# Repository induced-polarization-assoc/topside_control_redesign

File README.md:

View this project on [CADLAB.io](https://cadlab.io/project/22681). 

# topside_control_redesign
Contains CAD, board, and schematics as well as development notes and firmware associated with the different modules of the system.

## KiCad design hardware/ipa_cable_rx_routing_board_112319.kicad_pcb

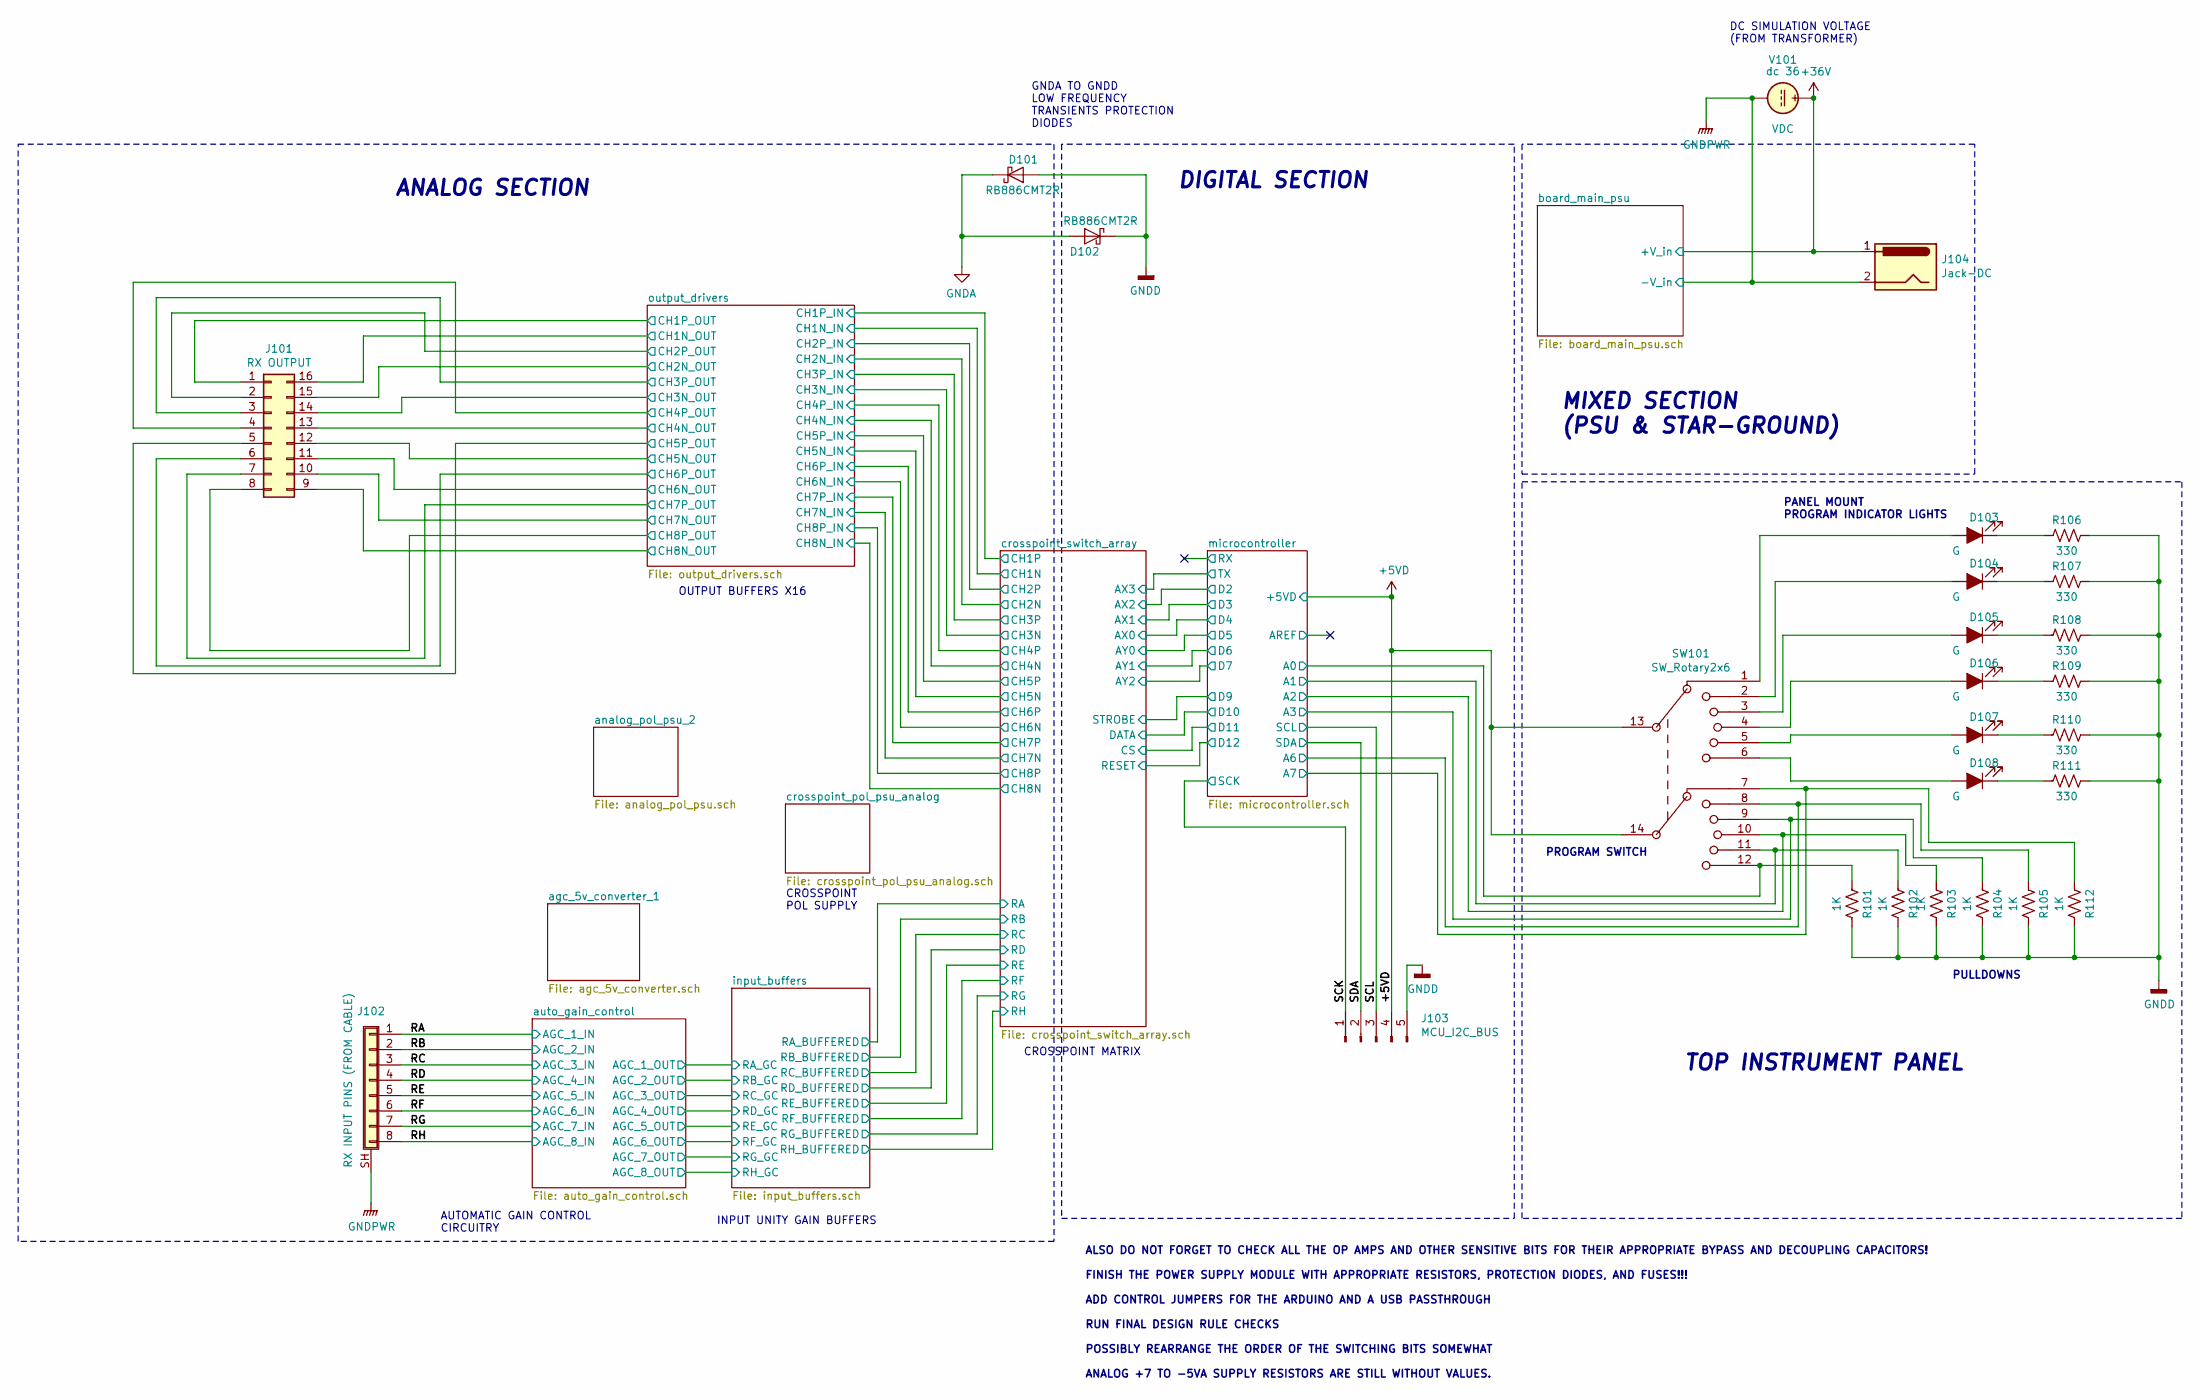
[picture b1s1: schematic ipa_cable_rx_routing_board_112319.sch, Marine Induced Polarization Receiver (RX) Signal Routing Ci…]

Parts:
D101, D102: RB886CMT2R; SOT-323_SC-70
D103, D104, D105, D106, D107, D108: G; PinHeader_1x02_P1.27mm_Vertical_SMD_Pin1Left
J101: RX OUTPUT; Samtec_HLE-108-02-xxx-DV-BE_2x08_P2.54mm_Horizontal
J102: RX INPUT PINS (FROM CABLE); Samtec_LSHM-105-xx.x-x-DV-S_2x05-1SH_P0.50mm_Vertical
J103: MCU_I2C_BUS; PinHeader_1x05_P1.27mm_Vertical_SMD_Pin1Right
J104: Jack-DC; TerminalBlock_TE_282834-3_1x03_P2.54mm_Horizontal
R101, R102, R103, R104, R105, R112: 1K; R_0805_2012Metric
R106, R107, R108, R109, R110, R111: 330; R_0805_2012Metric
SW101: SW_Rotary2x6; IDC-Header_2x07_P2.54mm_Vertical
V101: VDC; Symbol_GNU-Logo_SilkscreenTop

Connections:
+5VD: J103.4, SW101.13, SW101.14; also elsewhere on the board
+36V: J104.1, V101.1; also elsewhere on the board
/RA: J102.1; also elsewhere on the board
/RB: J102.2; also elsewhere on the board
/RC: J102.3; also elsewhere on the board
/RD: J102.4; also elsewhere on the board
/RE: J102.5; also elsewhere on the board
/RF: J102.6; also elsewhere on the board
/RG: J102.7; also elsewhere on the board
/RH: J102.8; also elsewhere on the board
/SCK: J103.1; also elsewhere on the board
/SCL: J103.3; also elsewhere on the board
/SDA: J103.2; also elsewhere on the board
/microcontroller/A0: R101.2, SW101.12; also elsewhere on the board
/microcontroller/A1: R102.2, SW101.11; also elsewhere on the board
/microcontroller/A2: R103.2, SW101.10; also elsewhere on the board
/microcontroller/A3: R104.2, SW101.9; also elsewhere on the board
/microcontroller/A6: R105.2, SW101.8; also elsewhere on the board
/microcontroller/A7: R112.2, SW101.7; also elsewhere on the board
/output_drivers/CH1N_OUT: J101.16; also elsewhere on the board
/output_drivers/CH1P_OUT: J101.1; also elsewhere on the board
/output_drivers/CH2N_OUT: J101.15; also elsewhere on the board
/output_drivers/CH2P_OUT: J101.2; also elsewhere on the board
/output_drivers/CH3N_OUT: J101.14; also elsewhere on the board
/output_drivers/CH3P_OUT: J101.3; also elsewhere on the board
/output_drivers/CH4N_OUT: J101.13; also elsewhere on the board
/output_drivers/CH4P_OUT: J101.4; also elsewhere on the board
/output_drivers/CH5N_OUT: J101.12; also elsewhere on the board
/output_drivers/CH5P_OUT: J101.5; also elsewhere on the board
/output_drivers/CH6N_OUT: J101.11; also elsewhere on the board
/output_drivers/CH6P_OUT: J101.6; also elsewhere on the board
/output_drivers/CH7N_OUT: J101.10; also elsewhere on the board
/output_drivers/CH7P_OUT: J101.7; also elsewhere on the board
/output_drivers/CH8N_OUT: J101.9; also elsewhere on the board
/output_drivers/CH8P_OUT: J101.8; also elsewhere on the board
GNDA: D101.1 (K), D102.2 (A); also elsewhere on the board
GNDD: D101.2 (A), D102.1 (K), J103.5, R101.1, R102.1, R103.1, R104.1, R105.1, R106.1, R107.1, R108.1, R109.1, R110.1, R111.1, R112.1; also elsewhere on the board
GNDPWR: J102.SH (Shield), J104.2, V101.2; also elsewhere on the board
unnamed: D103.1 (K), R106.2
unnamed: D103.2 (A), SW101.1
unnamed: D104.1 (K), R107.2
unnamed: D104.2 (A), SW101.2
unnamed: D105.1 (K), R108.2
unnamed: D105.2 (A), SW101.3
unnamed: D106.1 (K), R109.2
unnamed: D106.2 (A), SW101.4
unnamed: D107.1 (K), R110.2
unnamed: D107.2 (A), SW101.5
unnamed: D108.1 (K), R111.2
unnamed: D108.2 (A), SW101.6

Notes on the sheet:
INPUT UNITY GAIN BUFFERS
CROSSPOINT MATRIX
ALSO DO NOT FORGET TO CHECK ALL THE OP AMPS AND OTHER SENSITIVE BITS FOR THEIR APPROPRIATE BYPASS AND DECOUPLING CAPACITORS! FINISH THE POWER SUPPLY MODULE WITH APPROPRIATE RESISTORS, PROTECTION DIODES, AND FUSES!!! ADD CONTROL JUMPERS FOR THE ARDUINO AND A USB PASSTHROUGH RUN FINAL DESIGN RULE CHE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
OUTPUT BUFFERS X16
CROSSPOINT POL SUPPLY
DIGITAL SECTION
ANALOG SECTION
MIXED SECTION (PSU & STAR-GROUND)
PROGRAM SWITCH
PANEL MOUNT PROGRAM INDICATOR LIGHTS
TOP INSTRUMENT PANEL
PULLDOWNS
AUTOMATIC GAIN CONTROL CIRCUITRY
GNDA TO GNDD LOW FREQUENCY TRANSIENTS PROTECTION DIODES
DC SIMULATION VOLTAGE (FROM TRANSFORMER)

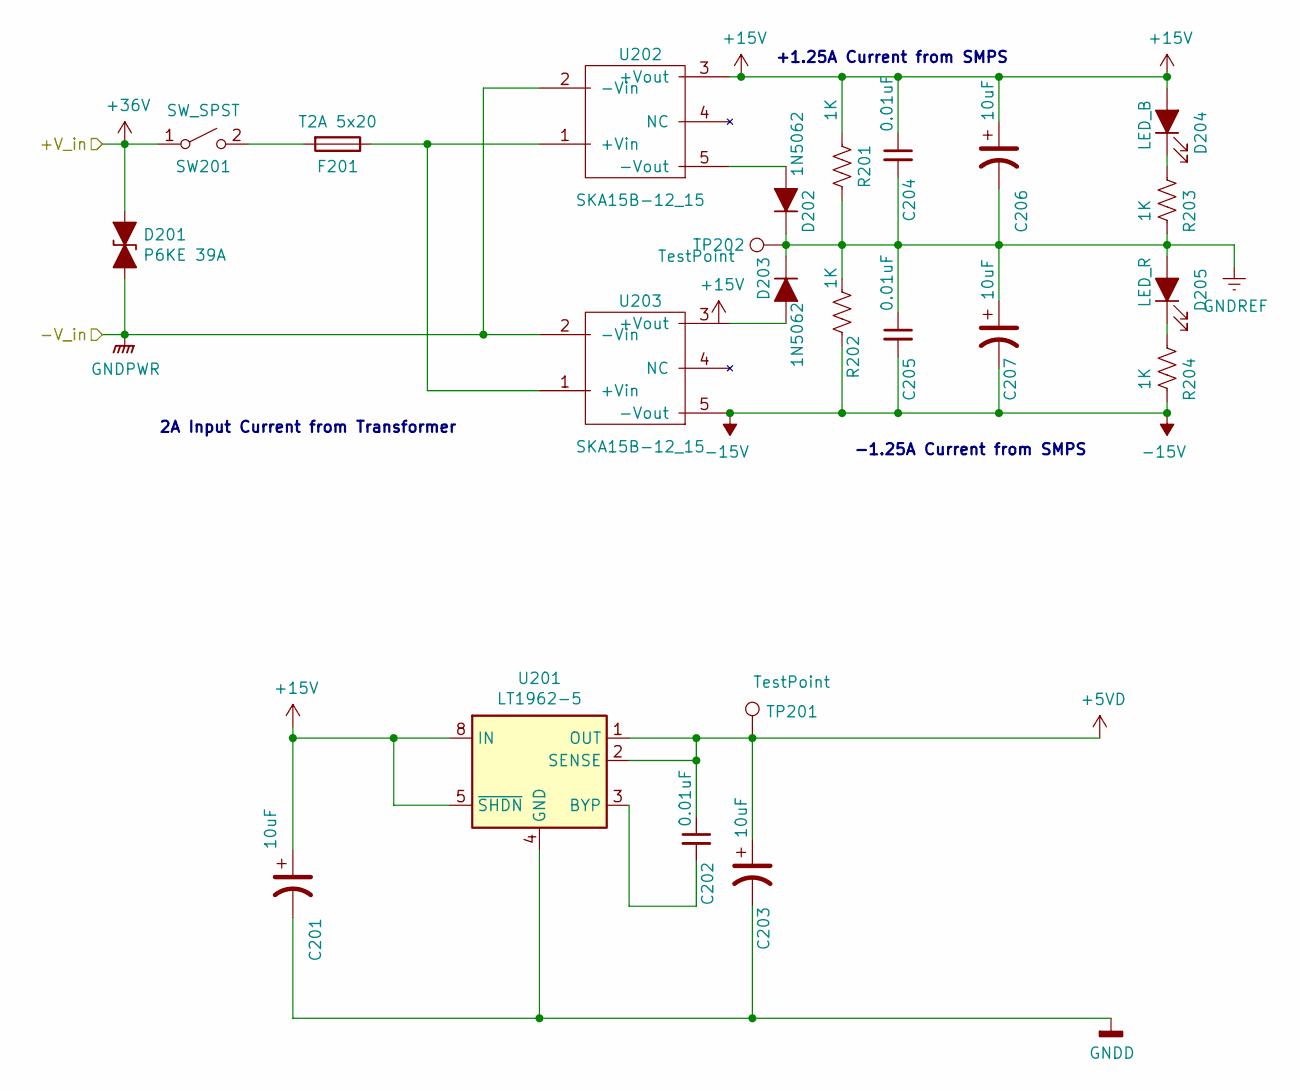
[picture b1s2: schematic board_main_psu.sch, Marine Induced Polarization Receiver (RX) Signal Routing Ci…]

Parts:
C201, C203, C206, C207: 10uF; CP_Elec_4x5.4
C202, C204, C205: 0.01uF; C_0805_2012Metric
D201: P6KE 39A; D_SMB
D202, D203: 1N5062; D_DO-15_P12.70mm_Horizontal
D204: LED_B; PinHeader_1x02_P1.27mm_Vertical_SMD_Pin1Left
D205: LED_R; PinHeader_1x02_P1.27mm_Vertical_SMD_Pin1Left
F201: T2A 5x20; Fuse_BelFuse_0ZRE0125FF_L21.2mm_W5.3mm
R201, R202, R203, R204: 1K; R_0805_2012Metric
SW201: SW_SPST; PinHeader_1x02_P1.27mm_Vertical_SMD_Pin1Left
TP201, TP202: TestPoint; TestPoint_Pad_D2.0mm
U201: LT1962-5; MSOP-8_3x3mm_P0.65mm
U202, U203: SKA15B-12_15; Converter_DCDC_MEANWELL_SKA15B_XXX_THT

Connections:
+5VD: C202.1, C203.1, TP201.1, U201.1 (OUT), U201.2 (SENSE); also elsewhere on the board
+15V: C201.1, C204.1, C206.1, D204.2 (A), R201.1, U201.5 (~SHDN), U201.8 (IN), U202.3 (+Vout); also elsewhere on the board
+36V: D201.1 (A1), SW201.1 (A); also elsewhere on the board
-15V: C205.2, C207.2, R202.2, R204.2, U203.5 (-Vout); also elsewhere on the board
GNDD: C201.2, C203.2, U201.4 (GND); also elsewhere on the board
GNDPWR: D201.2 (A2), U202.2 (-Vin), U203.2 (-Vin); also elsewhere on the board
GNDREF: C204.2, C205.1, C206.2, C207.1, D202.1 (K), D203.1 (K), D205.2 (A), R201.2, R202.1, R203.2, TP202.1
unnamed: C202.2, U201.3 (BYP)
unnamed: D202.2 (A), U202.5 (-Vout)
unnamed: D203.2 (A), U203.3 (+Vout)
unnamed: D204.1 (K), R203.1
unnamed: D205.1 (K), R204.1
unnamed: F201.1, U202.1 (+Vin), U203.1 (+Vin)
unnamed: F201.2, SW201.2 (B)

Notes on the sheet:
2A Input Current from Transformer
+1.25A Current from SMPS
-1.25A Current from SMPS

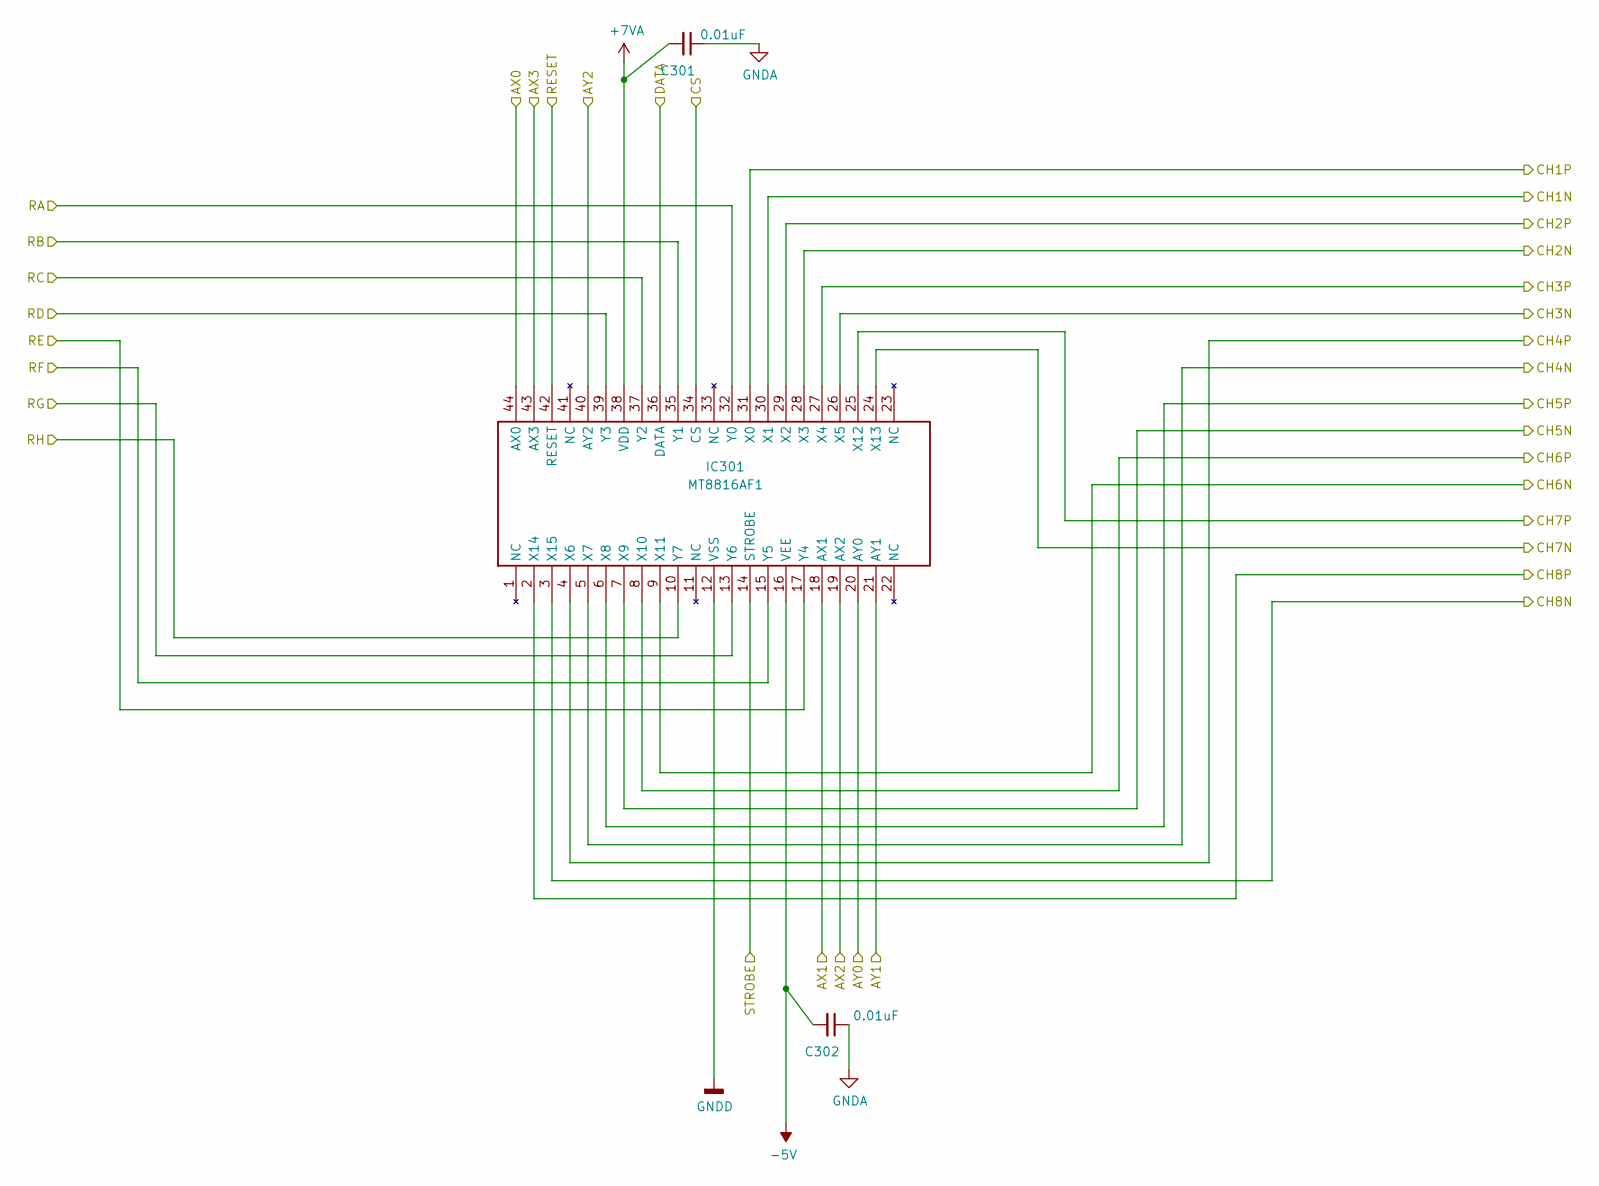
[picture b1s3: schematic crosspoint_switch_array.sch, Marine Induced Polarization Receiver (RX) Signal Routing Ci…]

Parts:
C301, C302: 0.01uF; C_0805_2012Metric
IC301: MT8816AF1; TQFP-44_10x10mm_P0.8mm

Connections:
+7VA: C301.2, IC301.38 (VDD); also elsewhere on the board
-5V: C302.2, IC301.16 (VEE); also elsewhere on the board
/crosspoint_switch_array/AX0: IC301.44 (AX0); also elsewhere on the board
/crosspoint_switch_array/AX1: IC301.18 (AX1); also elsewhere on the board
/crosspoint_switch_array/AX2: IC301.19 (AX2); also elsewhere on the board
/crosspoint_switch_array/AX3: IC301.43 (AX3); also elsewhere on the board
/crosspoint_switch_array/AY0: IC301.20 (AY0); also elsewhere on the board
/crosspoint_switch_array/AY1: IC301.21 (AY1); also elsewhere on the board
/crosspoint_switch_array/AY2: IC301.40 (AY2); also elsewhere on the board
/crosspoint_switch_array/CH1N: IC301.30 (X1); also elsewhere on the board
/crosspoint_switch_array/CH1P: IC301.31 (X0); also elsewhere on the board
/crosspoint_switch_array/CH2N: IC301.28 (X3); also elsewhere on the board
/crosspoint_switch_array/CH2P: IC301.29 (X2); also elsewhere on the board
/crosspoint_switch_array/CH3N: IC301.26 (X5); also elsewhere on the board
/crosspoint_switch_array/CH3P: IC301.27 (X4); also elsewhere on the board
/crosspoint_switch_array/CH4N: IC301.5 (X7); also elsewhere on the board
/crosspoint_switch_array/CH4P: IC301.4 (X6); also elsewhere on the board
/crosspoint_switch_array/CH5N: IC301.7 (X9); also elsewhere on the board
/crosspoint_switch_array/CH5P: IC301.6 (X8); also elsewhere on the board
/crosspoint_switch_array/CH6N: IC301.9 (X11); also elsewhere on the board
/crosspoint_switch_array/CH6P: IC301.8 (X10); also elsewhere on the board
/crosspoint_switch_array/CH7N: IC301.24 (X13); also elsewhere on the board
/crosspoint_switch_array/CH7P: IC301.25 (X12); also elsewhere on the board
/crosspoint_switch_array/CH8N: IC301.3 (X15); also elsewhere on the board
/crosspoint_switch_array/CH8P: IC301.2 (X14); also elsewhere on the board
/crosspoint_switch_array/CS: IC301.34 (CS); also elsewhere on the board
/crosspoint_switch_array/RA: IC301.32 (Y0); also elsewhere on the board
/crosspoint_switch_array/RB: IC301.35 (Y1); also elsewhere on the board
/crosspoint_switch_array/RC: IC301.37 (Y2); also elsewhere on the board
/crosspoint_switch_array/RD: IC301.39 (Y3); also elsewhere on the board
/crosspoint_switch_array/RE: IC301.17 (Y4); also elsewhere on the board
/crosspoint_switch_array/RF: IC301.15 (Y5); also elsewhere on the board
/crosspoint_switch_array/RG: IC301.13 (Y6); also elsewhere on the board
/crosspoint_switch_array/RH: IC301.10 (Y7); also elsewhere on the board
/microcontroller/D9: IC301.14 (STROBE); also elsewhere on the board
/microcontroller/D10: IC301.36 (DATA); also elsewhere on the board
/microcontroller/D12: IC301.42 (RESET); also elsewhere on the board
GNDA: C301.1, C302.1; also elsewhere on the board
GNDD: IC301.12 (VSS); also elsewhere on the board

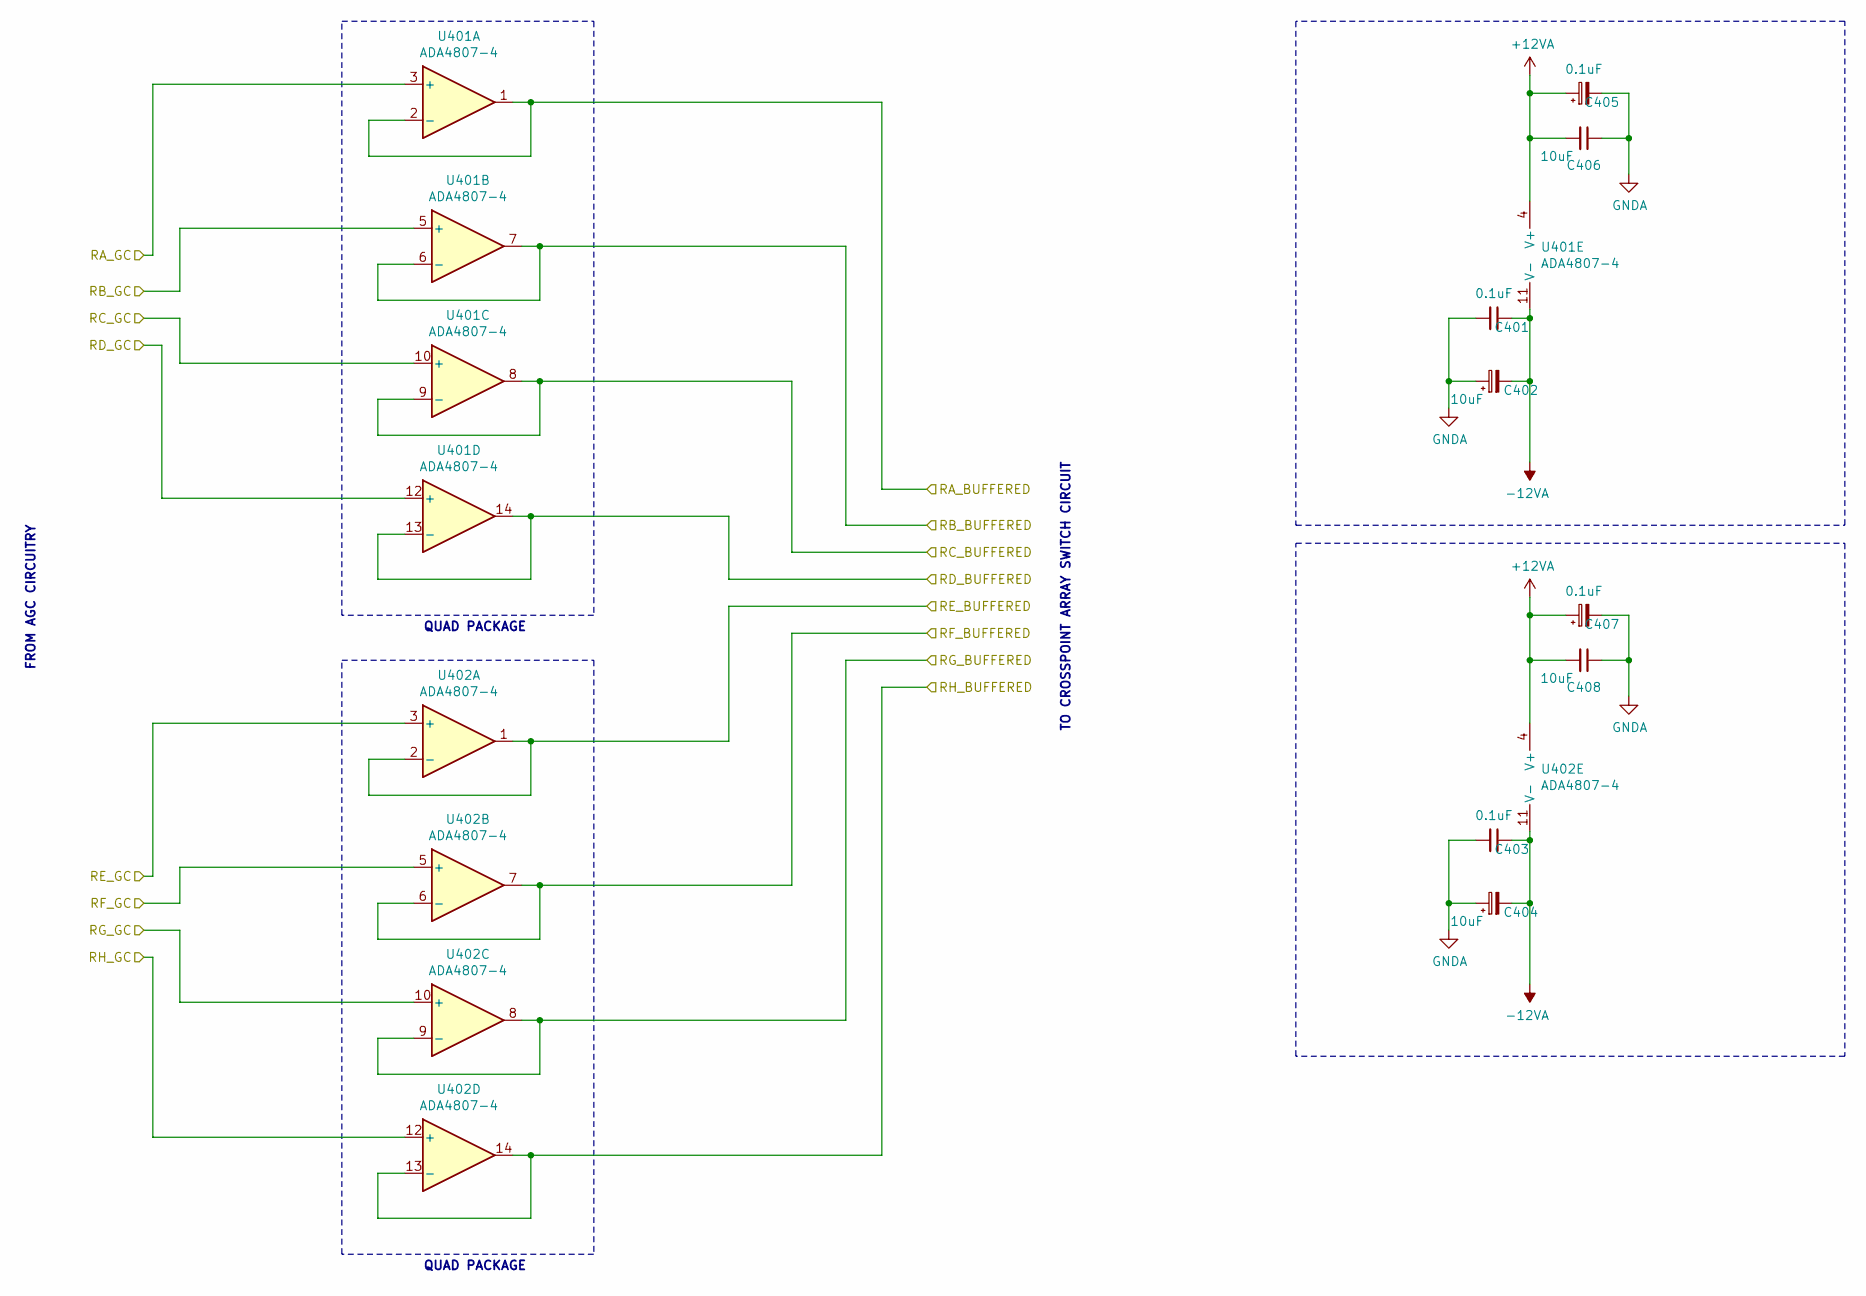
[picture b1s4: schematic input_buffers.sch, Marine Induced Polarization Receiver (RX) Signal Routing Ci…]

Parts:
C401, C403, C405, C407: 0.1uF; C_0805_2012Metric
C402, C404, C406, C408: 10uF; CP_Elec_4x5.4
U401, U402: ADA4807-4; TSSOP-14_4.4x5mm_P0.65mm

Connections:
+12VA: C405.1, C406.2, C407.1, C408.2, U401.4 (V+), U402.4 (V+); also elsewhere on the board
-12VA: C401.1, C402.2, C403.1, C404.2, U401.11 (V-), U402.11 (V-); also elsewhere on the board
/auto_gain_control/AGC_1_OUT: U401.3 (+); also elsewhere on the board
/auto_gain_control/AGC_2_OUT: U401.5 (+); also elsewhere on the board
/auto_gain_control/AGC_3_OUT: U401.10 (+); also elsewhere on the board
/auto_gain_control/AGC_4_OUT: U401.12 (+); also elsewhere on the board
/auto_gain_control/AGC_5_OUT: U402.3 (+); also elsewhere on the board
/auto_gain_control/AGC_6_OUT: U402.5 (+); also elsewhere on the board
/auto_gain_control/AGC_7_OUT: U402.10 (+); also elsewhere on the board
/auto_gain_control/AGC_8_OUT: U402.12 (+); also elsewhere on the board
/crosspoint_switch_array/RA: U401.1, U401.2 (-); also elsewhere on the board
/crosspoint_switch_array/RB: U401.6 (-), U401.7; also elsewhere on the board
/crosspoint_switch_array/RC: U401.8, U401.9 (-); also elsewhere on the board
/crosspoint_switch_array/RD: U401.13 (-), U401.14; also elsewhere on the board
/crosspoint_switch_array/RE: U402.1, U402.2 (-); also elsewhere on the board
/crosspoint_switch_array/RF: U402.6 (-), U402.7; also elsewhere on the board
/crosspoint_switch_array/RG: U402.8, U402.9 (-); also elsewhere on the board
/crosspoint_switch_array/RH: U402.13 (-), U402.14; also elsewhere on the board
GNDA: C401.2, C402.1, C403.2, C404.1, C405.2, C406.1, C407.2, C408.1; also elsewhere on the board

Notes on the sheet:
QUAD PACKAGE
FROM AGC CIRCUITRY
TO CROSSPOINT ARRAY SWITCH CIRCUIT

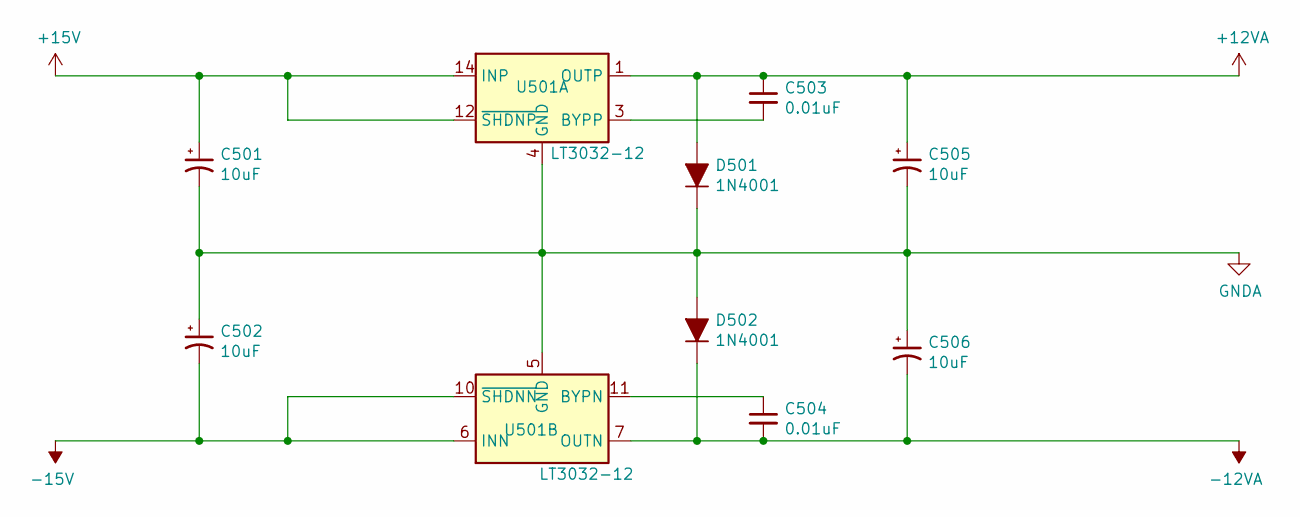
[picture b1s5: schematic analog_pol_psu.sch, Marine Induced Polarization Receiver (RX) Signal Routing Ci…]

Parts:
C501, C502, C505, C506: 10uF; CP_Elec_4x5.4
C503, C504: 0.01uF; C_0805_2012Metric
D501, D502: 1N4001; D_DO-41_SOD81_P10.16mm_Horizontal
U501: LT3032-12; Linear_DE14MA

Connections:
+12VA: C503.1, C505.1, D501.2 (A), U501.1 (OUTP); also elsewhere on the board
+15V: C501.1, U501.12 (~SHDNP), U501.14 (INP); also elsewhere on the board
-12VA: C504.2, C506.2, D502.1 (K), U501.7 (OUTN); also elsewhere on the board
-15V: C502.2, U501.6 (INN), U501.9 (INN), U501.10 (~SHDNN); also elsewhere on the board
GNDA: C501.2, C502.1, C505.2, C506.1, D501.1 (K), D502.2 (A), U501.4 (GND), U501.5 (GND); also elsewhere on the board
unnamed: C503.2, U501.3 (BYPP)
unnamed: C504.1, U501.11 (BYPN)

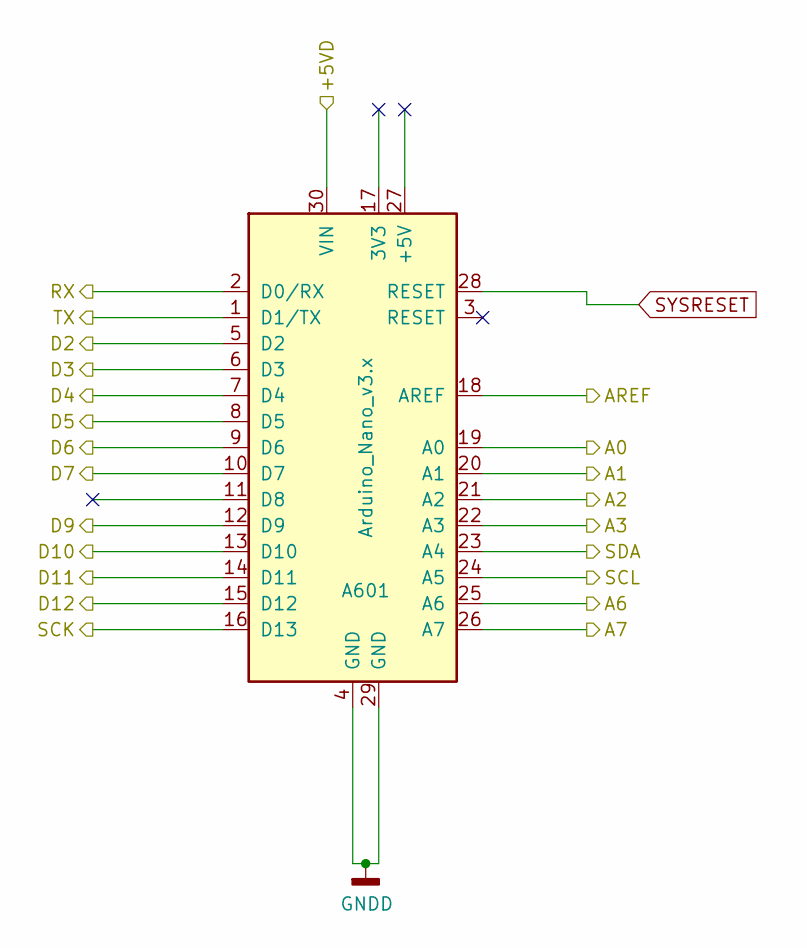
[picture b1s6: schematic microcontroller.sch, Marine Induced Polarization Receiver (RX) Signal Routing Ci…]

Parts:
A601: Arduino_Nano_v3.x; Arduino_Nano

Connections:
+5VD: A601.30 (VIN); also elsewhere on the board
/SCK: A601.16 (D13); also elsewhere on the board
/SCL: A601.24 (A5); also elsewhere on the board
/SDA: A601.23 (A4); also elsewhere on the board
/crosspoint_switch_array/AX0: A601.7 (D4); also elsewhere on the board
/crosspoint_switch_array/AX1: A601.6 (D3); also elsewhere on the board
/crosspoint_switch_array/AX2: A601.5 (D2); also elsewhere on the board
/crosspoint_switch_array/AX3: A601.1 (D1/TX); also elsewhere on the board
/crosspoint_switch_array/AY0: A601.8 (D5); also elsewhere on the board
/crosspoint_switch_array/AY1: A601.9 (D6); also elsewhere on the board
/crosspoint_switch_array/AY2: A601.10 (D7); also elsewhere on the board
/crosspoint_switch_array/CS: A601.14 (D11); also elsewhere on the board
/microcontroller/A0: A601.19 (A0); also elsewhere on the board
/microcontroller/A1: A601.20 (A1); also elsewhere on the board
/microcontroller/A2: A601.21 (A2); also elsewhere on the board
/microcontroller/A3: A601.22 (A3); also elsewhere on the board
/microcontroller/A6: A601.25 (A6); also elsewhere on the board
/microcontroller/A7: A601.26 (A7); also elsewhere on the board
/microcontroller/AREF: A601.18 (AREF)
/microcontroller/D9: A601.12 (D9); also elsewhere on the board
/microcontroller/D10: A601.13 (D10); also elsewhere on the board
/microcontroller/D12: A601.15 (D12); also elsewhere on the board
/microcontroller/RX: A601.2 (D0/RX)
GNDD: A601.4 (GND), A601.29 (GND); also elsewhere on the board
SYSRESET: A601.28 (RESET)

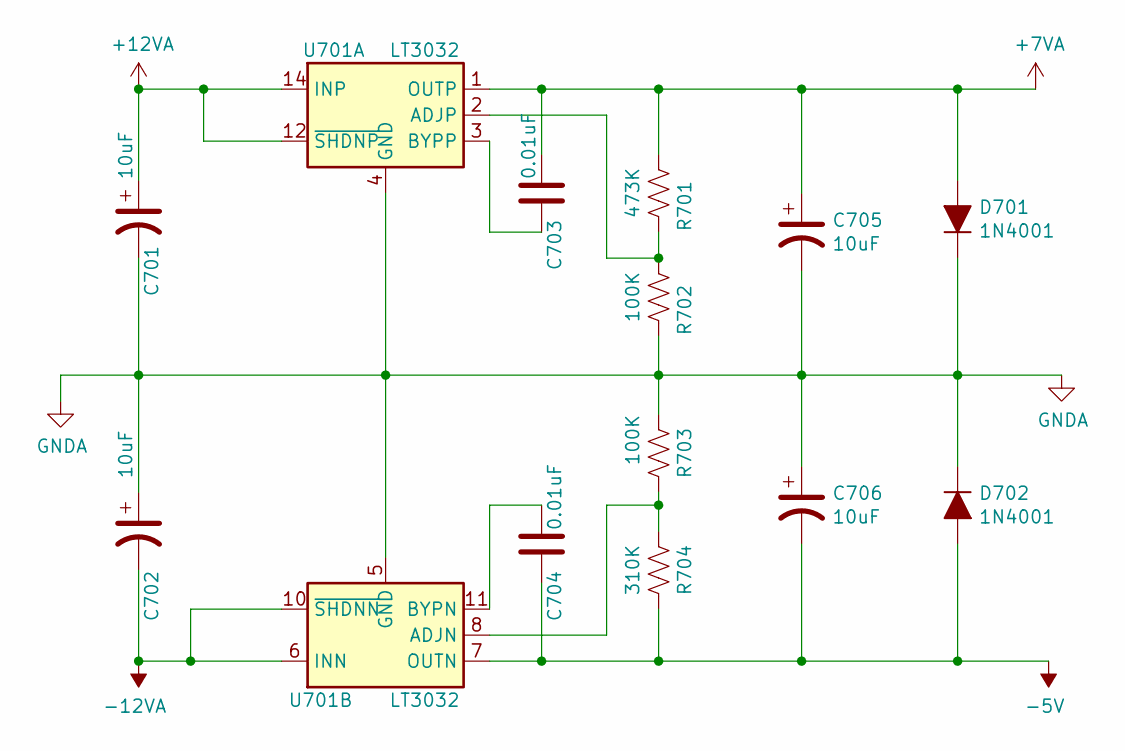
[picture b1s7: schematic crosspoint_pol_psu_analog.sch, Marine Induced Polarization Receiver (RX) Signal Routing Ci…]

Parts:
C701, C702, C705, C706: 10uF; CP_Elec_4x5.4
C703, C704: 0.01uF; C_0805_2012Metric
D701, D702: 1N4001; D_DO-41_SOD81_P10.16mm_Horizontal
R701: 473K; R_0805_2012Metric
R702, R703: 100K; R_0805_2012Metric
R704: 310K; R_0805_2012Metric
U701: LT3032; Linear_DE14MA

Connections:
+7VA: C703.1, C705.1, D701.2 (A), R701.1, U701.1 (OUTP); also elsewhere on the board
+12VA: C701.1, U701.12 (~SHDNP), U701.14 (INP); also elsewhere on the board
-5V: C704.2, C706.2, D702.2 (A), R704.2, U701.7 (OUTN); also elsewhere on the board
-12VA: C702.2, U701.6 (INN), U701.9 (INN), U701.10 (~SHDNN); also elsewhere on the board
GNDA: C701.2, C702.1, C705.2, C706.1, D701.1 (K), D702.1 (K), R702.2, R703.1, U701.4 (GND), U701.5 (GND); also elsewhere on the board
unnamed: C703.2, U701.3 (BYPP)
unnamed: C704.1, U701.11 (BYPN)
unnamed: R701.2, R702.1, U701.2 (ADJP)
unnamed: R703.2, R704.1, U701.8 (ADJN)

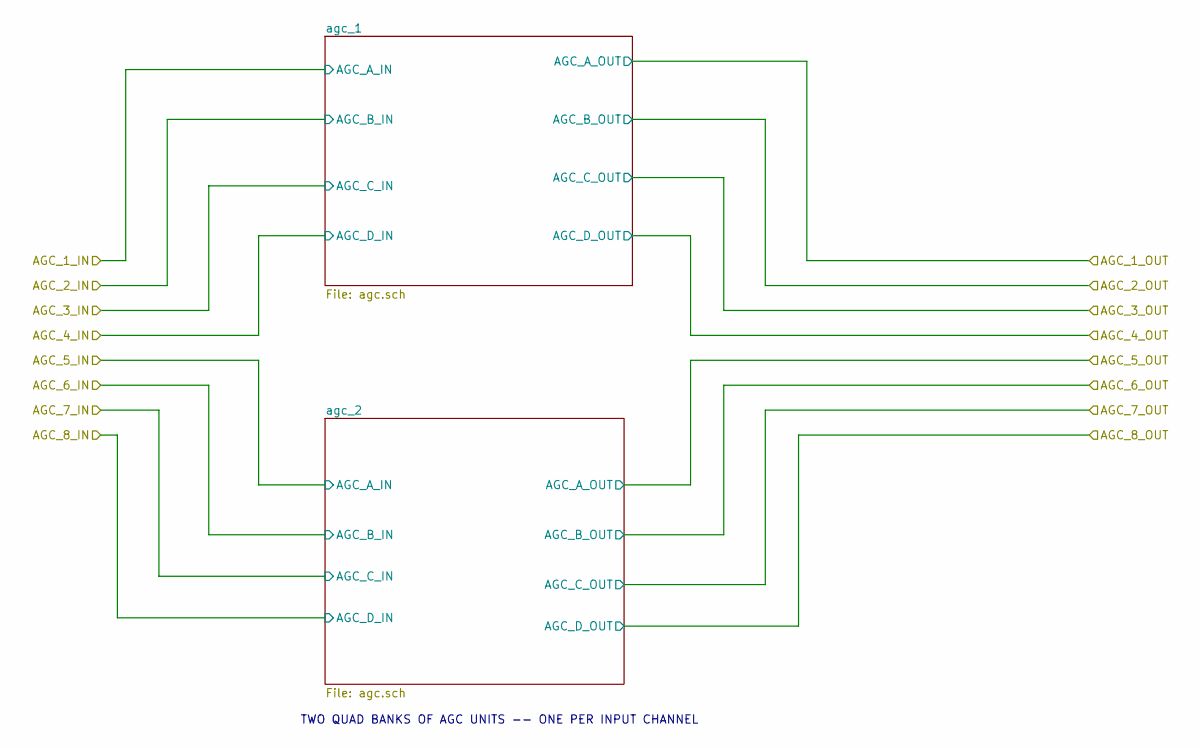
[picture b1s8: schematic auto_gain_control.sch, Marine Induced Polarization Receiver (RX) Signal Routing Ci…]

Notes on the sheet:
TWO QUAD BANKS OF AGC UNITS -- ONE PER INPUT CHANNEL

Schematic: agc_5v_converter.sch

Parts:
C1101, C1102, C1105, C1106: 10uF; CP_Elec_4x5.4
C1103, C1104: 0.01uF; C_0805_2012Metric
U1101: LT3032-5; Linear_DE14MA

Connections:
+5VA: C1103.1, C1105.1, U1101.1 (OUTP); also elsewhere on the board
+12VA: C1101.1, U1101.12 (~SHDNP), U1101.14 (INP); also elsewhere on the board
-5VA: C1104.1, C1106.2, U1101.7 (OUTN); also elsewhere on the board
-12VA: C1102.2, U1101.6 (INN), U1101.9 (INN), U1101.10 (~SHDNN); also elsewhere on the board
GNDA: C1101.2, C1102.1, C1105.2, C1106.1, U1101.4 (GND), U1101.5 (GND); also elsewhere on the board
unnamed: C1103.2, U1101.3 (BYPP)
unnamed: C1104.2, U1101.11 (BYPN)

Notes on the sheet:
OUTPUTS +/-5VDC at 150mA with 20uV_RMS noise
AGC UNIT POL +/-5V

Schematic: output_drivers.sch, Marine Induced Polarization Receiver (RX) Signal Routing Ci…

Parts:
C1201, C1203, C1205, C1207, C1209, C1211, C1213, C1215: 0.1uF; C_0805_2012Metric
C1202, C1204, C1206, C1208, C1210, C1212, C1214, C1216: 10uF; CP_Elec_4x5.4
U1201, U1202, U1203, U1204: ADA4807-4; TSSOP-14_4.4x5mm_P0.65mm

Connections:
+12VA: C1201.1, C1202.2, C1205.1, C1206.2, C1209.1, C1210.2, C1213.1, C1214.2, U1201.4 (V+), U1202.4 (V+), U1203.4 (V+), U1204.4 (V+); also elsewhere on the board
-12VA: C1203.1, C1204.2, C1207.1, C1208.2, C1211.1, C1212.2, C1215.1, C1216.2, U1201.11 (V-), U1202.11 (V-), U1203.11 (V-), U1204.11 (V-); also elsewhere on the board
/crosspoint_switch_array/CH1N: U1201.5 (+); also elsewhere on the board
/crosspoint_switch_array/CH1P: U1201.3 (+); also elsewhere on the board
/crosspoint_switch_array/CH2N: U1201.12 (+); also elsewhere on the board
/crosspoint_switch_array/CH2P: U1201.10 (+); also elsewhere on the board
/crosspoint_switch_array/CH3N: U1203.5 (+); also elsewhere on the board
/crosspoint_switch_array/CH3P: U1203.3 (+); also elsewhere on the board
/crosspoint_switch_array/CH4N: U1203.12 (+); also elsewhere on the board
/crosspoint_switch_array/CH4P: U1203.10 (+); also elsewhere on the board
/crosspoint_switch_array/CH5N: U1202.5 (+); also elsewhere on the board
/crosspoint_switch_array/CH5P: U1202.3 (+); also elsewhere on the board
/crosspoint_switch_array/CH6N: U1202.12 (+); also elsewhere on the board
/crosspoint_switch_array/CH6P: U1202.10 (+); also elsewhere on the board
/crosspoint_switch_array/CH7N: U1204.5 (+); also elsewhere on the board
/crosspoint_switch_array/CH7P: U1204.3 (+); also elsewhere on the board
/crosspoint_switch_array/CH8N: U1204.12 (+); also elsewhere on the board
/crosspoint_switch_array/CH8P: U1204.10 (+); also elsewhere on the board
/output_drivers/CH1N_OUT: U1201.6 (-), U1201.7; also elsewhere on the board
/output_drivers/CH1P_OUT: U1201.1, U1201.2 (-); also elsewhere on the board
/output_drivers/CH2N_OUT: U1201.13 (-), U1201.14; also elsewhere on the board
/output_drivers/CH2P_OUT: U1201.8, U1201.9 (-); also elsewhere on the board
/output_drivers/CH3N_OUT: U1203.6 (-), U1203.7; also elsewhere on the board
/output_drivers/CH3P_OUT: U1203.1, U1203.2 (-); also elsewhere on the board
/output_drivers/CH4N_OUT: U1203.13 (-), U1203.14; also elsewhere on the board
/output_drivers/CH4P_OUT: U1203.8, U1203.9 (-); also elsewhere on the board
/output_drivers/CH5N_OUT: U1202.6 (-), U1202.7; also elsewhere on the board
/output_drivers/CH5P_OUT: U1202.1, U1202.2 (-); also elsewhere on the board
/output_drivers/CH6N_OUT: U1202.13 (-), U1202.14; also elsewhere on the board
/output_drivers/CH6P_OUT: U1202.8, U1202.9 (-); also elsewhere on the board
/output_drivers/CH7N_OUT: U1204.6 (-), U1204.7; also elsewhere on the board
/output_drivers/CH7P_OUT: U1204.1, U1204.2 (-); also elsewhere on the board
/output_drivers/CH8N_OUT: U1204.13 (-), U1204.14; also elsewhere on the board
/output_drivers/CH8P_OUT: U1204.8, U1204.9 (-); also elsewhere on the board
GNDA: C1201.2, C1202.1, C1203.2, C1204.1, C1205.2, C1206.1, C1207.2, C1208.1, C1209.2, C1210.1, C1211.2, C1212.1, C1213.2, C1214.1, C1215.2, C1216.1; also elsewhere on the board

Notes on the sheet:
QUAD BUFFER 1
QUAD BUFFER 2
QUAD BUFFER 3
QUAD BUFFER 4
TO RX OUTPUT PANEL
FROM CROSSPOINT SWITCH ARRAY CIRCUITS
QUAD BUFFER 4 POWER AND BYPASS
QUAD BUFFER 2 POWER AND BYPASS
QUAD BUFFER 1 POWER AND BYPASS
QUAD BUFFER 3 POWER AND BYPASS
